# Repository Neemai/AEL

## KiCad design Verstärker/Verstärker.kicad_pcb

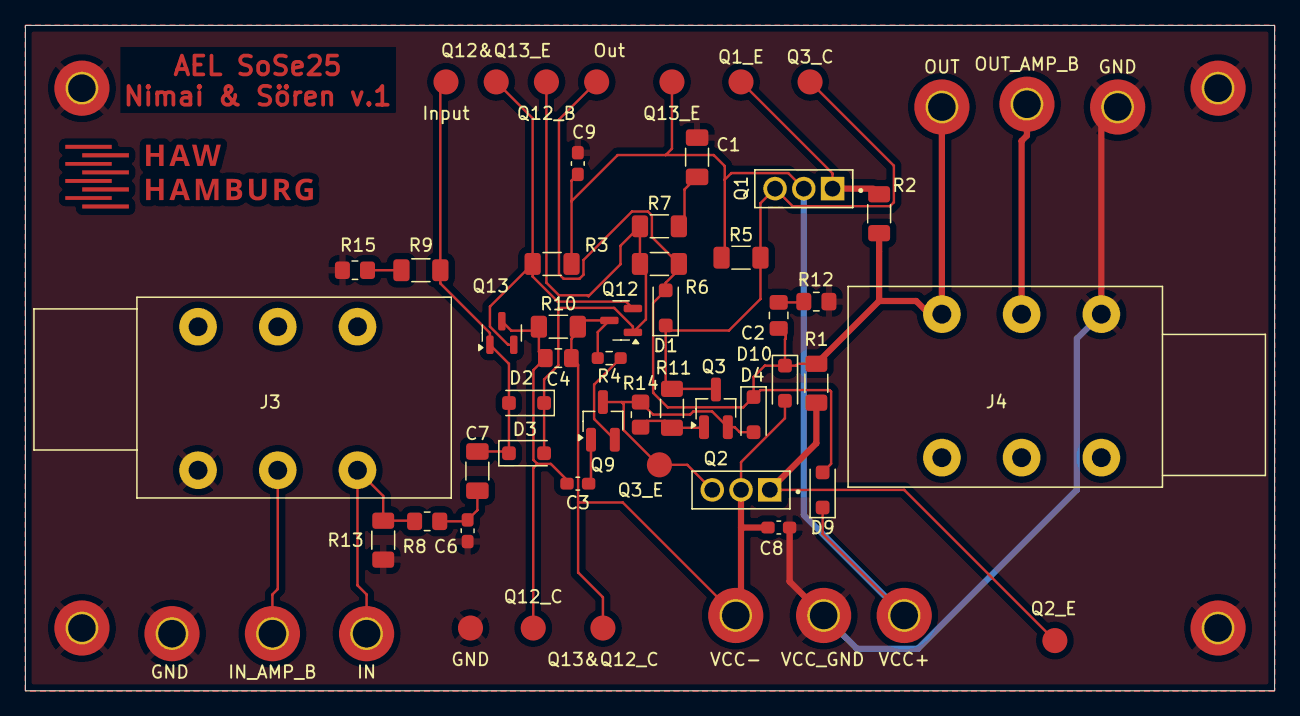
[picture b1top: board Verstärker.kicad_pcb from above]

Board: 2 copper layers, 99.5 x 53.0 mm, 62 parts (0 on the bottom side), 22 nets.

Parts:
C1: 100u; C_1206_3216Metric_Pad1.33x1.80mm_HandSolder
C2, C4: 10n; C_0805_2012Metric_Pad1.18x1.45mm_HandSolder
C3: 1n; C_0603_1608Metric_Pad1.08x0.95mm_HandSolder
C6: 220p; C_0603_1608Metric_Pad1.08x0.95mm_HandSolder
C7: 22u; C_1206_3216Metric_Pad1.33x1.80mm_HandSolder
C8, C9: 100n; C_0603_1608Metric_Pad1.08x0.95mm_HandSolder
D1, D2, D3, D4, D9, D10: SM4007PL; D_SOD-123F
GND: test_point; TestPoint_Pad_D2.0mm
GND4, GND5, GND6, GND7: Mounting Hole with connection; MountingHole_2.2mm_M2_Pad_TopBottom
GND#2, GND#3: Mounting Hole with connection; MountingHole_2.2mm_M2_Pad_TopBottom
IN: Mounting Hole with connection; MountingHole_2.2mm_M2_Pad_TopBottom
IN_AMP_B: Mounting Hole with connection; MountingHole_2.2mm_M2_Pad_TopBottom
Input: test_point; TestPoint_Pad_D2.0mm
J3, J4: ACJS-MHOM; Jack_6.35mm_Neutrik_NRJ6HM-1_Horizontal
OUT: Mounting Hole with connection; MountingHole_2.2mm_M2_Pad_TopBottom
OUT_AMP_B: Mounting Hole with connection; MountingHole_2.2mm_M2_Pad_TopBottom
Out: test_point; TestPoint_Pad_D2.0mm
Q1: MJE182G; TO229P780X300X1364-3
Q1_E, Q2_E, Q3_C, Q3_E, Q12&Q13_E, Q12_B, Q12_C, Q13&Q12_C, Q13_E: test_point; TestPoint_Pad_D2.0mm
Q2: MJE172G; TO229P780X300X1364-3
Q3, Q9: MMBT5551(RANGE:200-300); SOT-23_Handsoldering
Q12, Q13: MMBT5401; SOT-23
R1, R2: 10; R_1206_3216Metric_Pad1.30x1.75mm_HandSolder
R3: 4k7; R_1206_3216Metric_Pad1.30x1.75mm_HandSolder
R4: 75; R_0603_1608Metric_Pad0.98x0.95mm_HandSolder
R5, R7: 2k; R_1206_3216Metric_Pad1.30x1.75mm_HandSolder
R6, R9: 10k; R_1206_3216Metric_Pad1.30x1.75mm_HandSolder
R8, R15: 200; R_0805_2012Metric_Pad1.20x1.40mm_HandSolder
R10, R11: 1k; R_1206_3216Metric_Pad1.30x1.75mm_HandSolder
R12: 51; R_0805_2012Metric_Pad1.20x1.40mm_HandSolder
R13: 100k; R_1206_3216Metric_Pad1.30x1.75mm_HandSolder
R14: 510; R_0805_2012Metric_Pad1.20x1.40mm_HandSolder
VCC+: Mounting Hole with connection; MountingHole_2.2mm_M2_Pad_TopBottom
VCC-: Mounting Hole with connection; MountingHole_2.2mm_M2_Pad_TopBottom
VCC_GND: Mounting Hole with connection; MountingHole_2.2mm_M2_Pad_TopBottom

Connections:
GND: C1.1, C6.1, C8.1, C9.1, GND.1, GND4.1, GND5.1, GND6.1, GND7.1, GND#2.1, GND#3.1, J3.S, J4.S, R12.2, R13.1, R15.2, VCC_GND.1
unnamed: C1.2, R7.2
unnamed: C2.1, R12.1
unnamed: C6.2, C7.1, R8.2
unnamed: C2.2, D1.2 (A), D4.1 (K), D9.2 (A), D10.1 (K), J4.T, OUT.1, Out.1, R1.1, R2.2, R6.2
unnamed: D1.1 (K), Q1.3 (B), Q3.3 (C), Q3_C.1, R5.2, R11.1
unnamed: C7.2, D2.2 (A), D3.1 (K), Input.1, Q13.1 (B), R9.1
unnamed: D2.1 (K), D3.2 (A), Q12.1 (B), Q12_B.1, R6.1, R7.1
unnamed: D4.2 (A), Q2.3 (B), Q3.2 (E), Q3_E.1, Q9.3 (C), R14.2
unnamed: C9.2, D9.1 (K), Q1.2 (C), Q13_E.1, R3.1, R5.1, VCC+.1
unnamed: C4.1, C8.2, D10.2 (A), Q2.2 (C), Q12.3 (C), Q13&Q12_C.1, R4.2, R10.2, VCC-.1
unnamed: IN.1, J3.T, R8.1, R13.2
unnamed: IN_AMP_B.1, J3.R
unnamed: J4.R, OUT_AMP_B.1
unnamed: Q1.1 (E), Q1_E.1, R2.1
unnamed: Q2.1 (E), Q2_E.1, R1.2
unnamed: Q3.1 (B), R11.2, R14.1
unnamed: C3.1, Q9.1 (B)
unnamed: Q9.2 (E), R4.1
unnamed: Q12.2 (E), Q12&Q13_E.1, Q13.2 (E), R3.2
unnamed: C3.2, C4.2, Q12_C.1, Q13.3 (C), R10.1
unnamed: R9.2, R15.1

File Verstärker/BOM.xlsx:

Designator | Footprint | Quantity | Value | LCSC Part #
C1 | 1206 | 1 | 100u | C15008
C2, C4 | 0805 | 2 | 10n | C1710
C3 | 0603 | 1 | 1n | C1588
C6 | 0603 | 1 | 220p | C1603
C7 | 1206 | 1 | 22u | C12891
C8, C9 | 0603 | 2 | 100n | C14663
D1, D10, D2, D3, D4, D9 | D_SOD-123F | 6 | SM4007PL | C64898
J2, J3 | Jack_6.35mm_Neutrik_NRJ6HM-1_Horizontal | 2 | ACJS-MHOM | C4991596
Q1 | TO229P780X300X1364-3 | 1 | MJE182G | C27681
Q12, Q13 | SOT-23 | 2 | MMBT5401 | C8326
Q2 | TO229P780X300X1364-3 | 1 | MJE172G | C27682
Q3, Q9 | SOT-23 | 2 | MMBT5551(RANGE:200-300) | C2145
R1, R2 | 1206 | 2 | 10 | C17903
R10, R11 | 1206 | 2 | 1k | C4410
R12 | 0805 | 1 | 51 | C17738
R13 | 1206 | 1 | 100k | C17900
R14 | 0805 | 1 | 510 | C17734
R15, R8 | 0805 | 2 | 200 | C17540
R3 | 1206 | 1 | 4k7 | C17936
R4 | 0603 | 1 | 75 | C4275
R5, R7 | 1206 | 2 | 2k | C17944
R6, R9 | 1206 | 2 | 10k | C17902

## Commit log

2025-04-29 29.04. Ende der VL
2025-04-29 29.04. 15 Uhr
2025-05-04 04.05. PCB komplett
2025-05-06 dru Datei hinnzugefügt. Silcscreen der Testpoitns angepasst.
2025-05-06 Test
2025-05-06 Update README.md
    Test
2025-05-06 Test2
2025-05-06 Dings
2025-05-06 Weiter aufgeräumt
2025-05-06 Weiter aufgeräumt2
2025-05-06 do not populate testpoints
2025-05-06 Alles auf 10cm Breite geschrumpft. Keine Vias
2025-05-09 Erste Korrektur Revesion
2025-05-09 Zweite Korrektur
2025-05-12 Testweise Produktionsdaten exportiert, muss später überschrieben werden. Fehler festgestellt in nicht vorhandenen JLCPCB Nummern.
2025-05-12 fehlerhfate MPN Einträge geändert. Produktionsdaten ausgegeben
2025-05-12 nochmal gespeichert
2025-05-12 do not include in position files bei testpoints
2025-05-12 kleine Fehlerkorrektur
2025-05-12 produktions und gerber daten exportiert
2025-06-03 Version 1.1 Kondennsator C4 richtig, Beschriftung richtig, Ränder richtig
